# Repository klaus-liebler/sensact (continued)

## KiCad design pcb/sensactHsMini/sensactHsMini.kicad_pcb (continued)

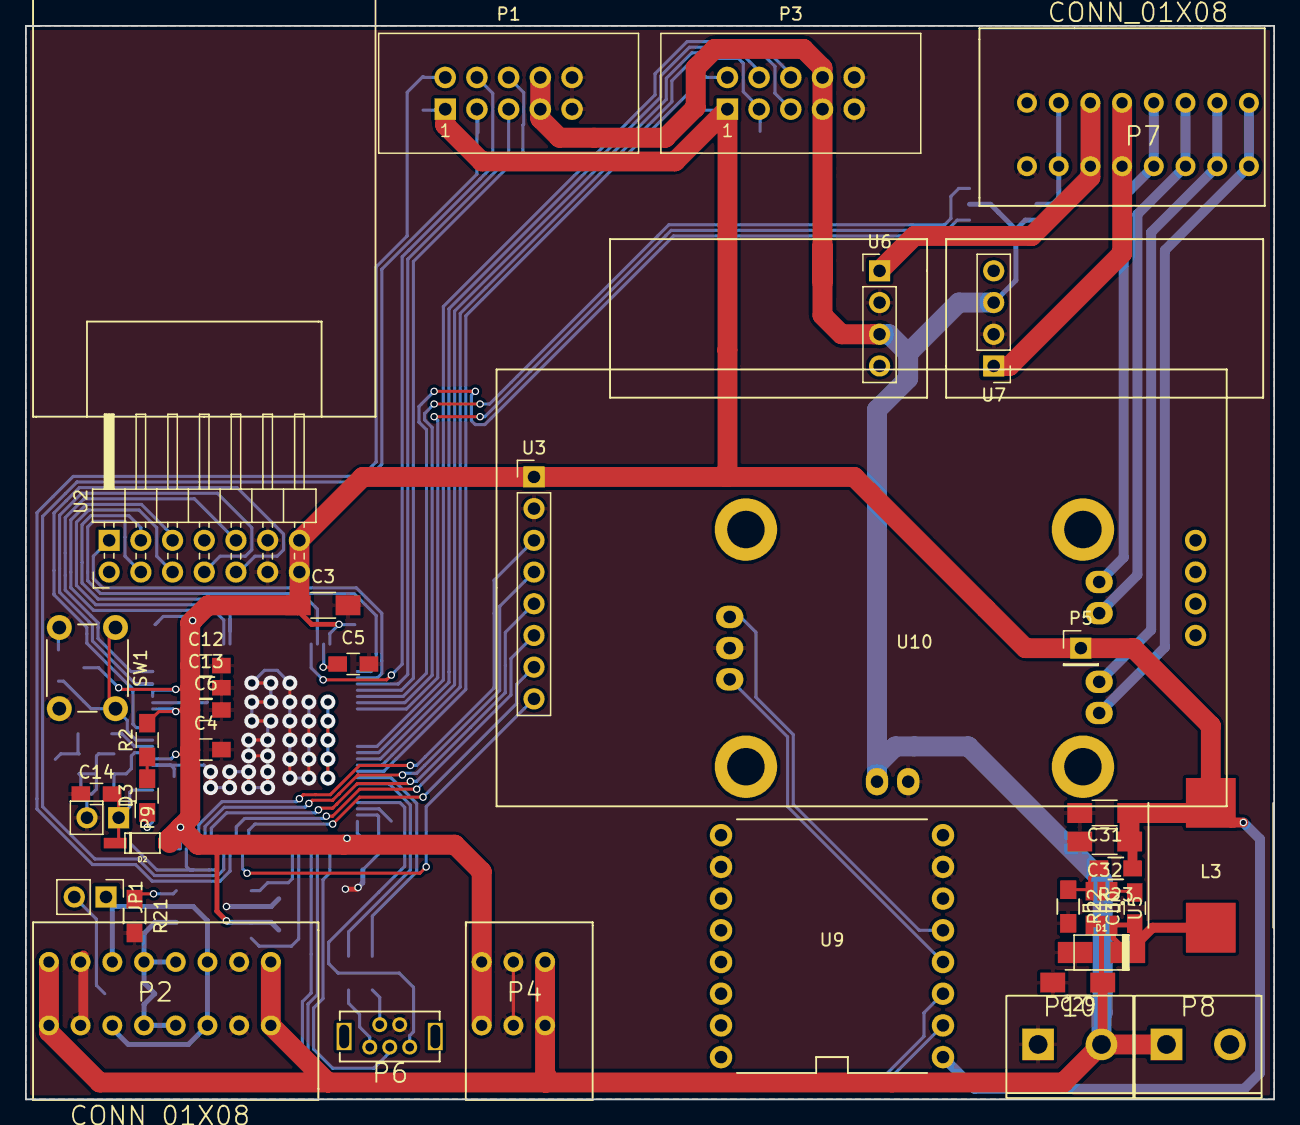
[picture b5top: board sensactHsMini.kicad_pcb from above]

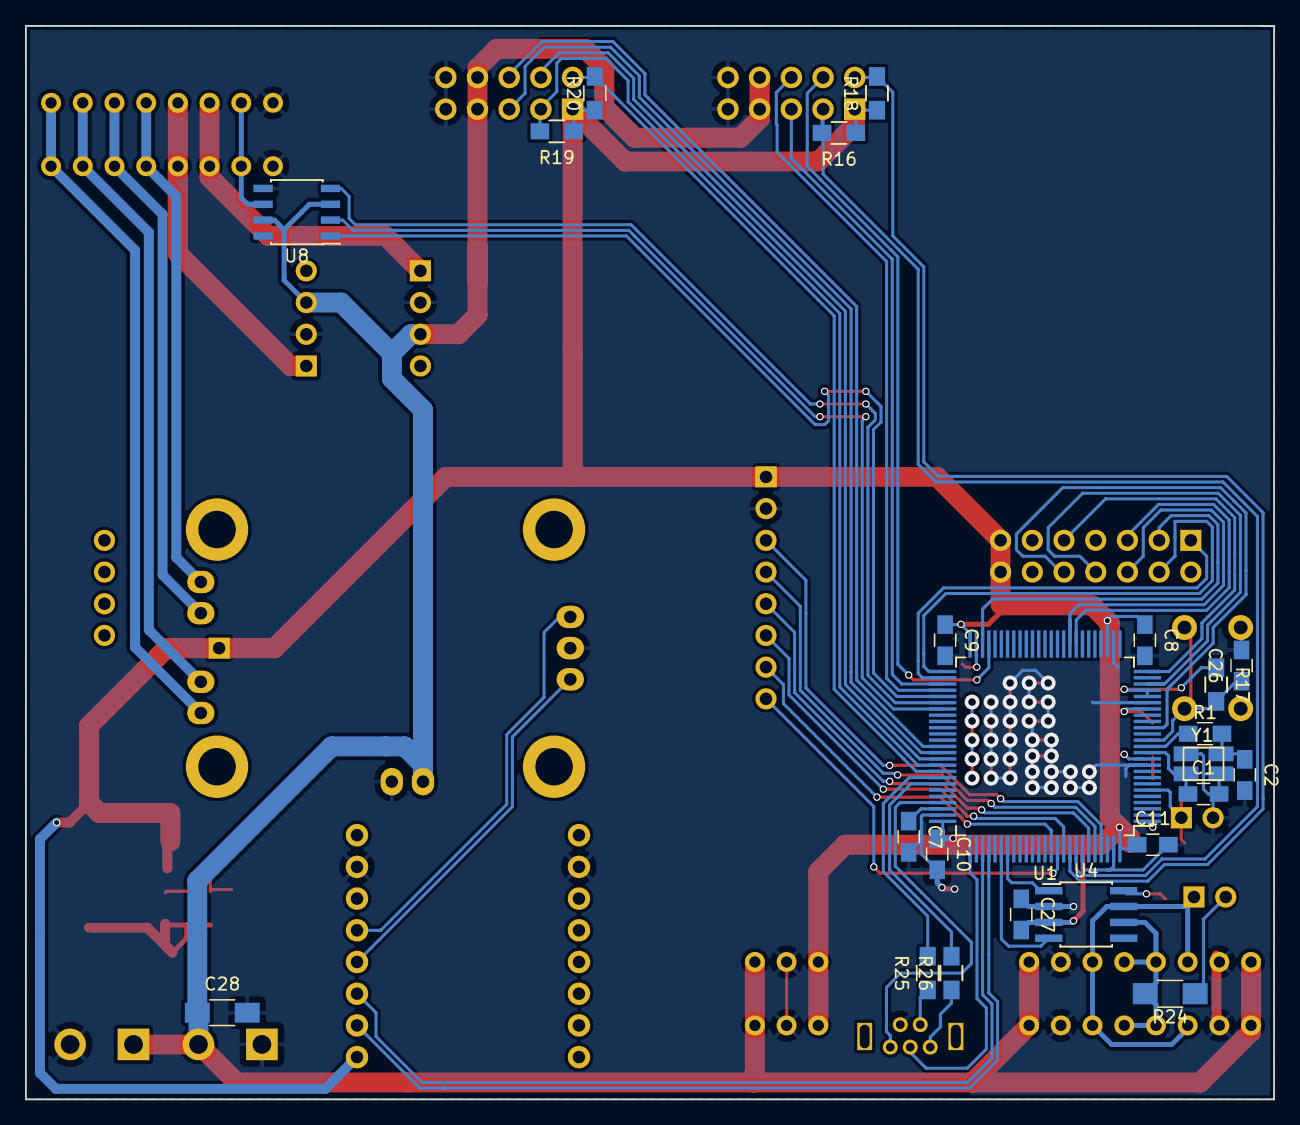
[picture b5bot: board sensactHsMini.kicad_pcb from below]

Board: 2 copper layers, 100.0 x 86.0 mm, 61 parts (23 on the bottom side), 65 nets.

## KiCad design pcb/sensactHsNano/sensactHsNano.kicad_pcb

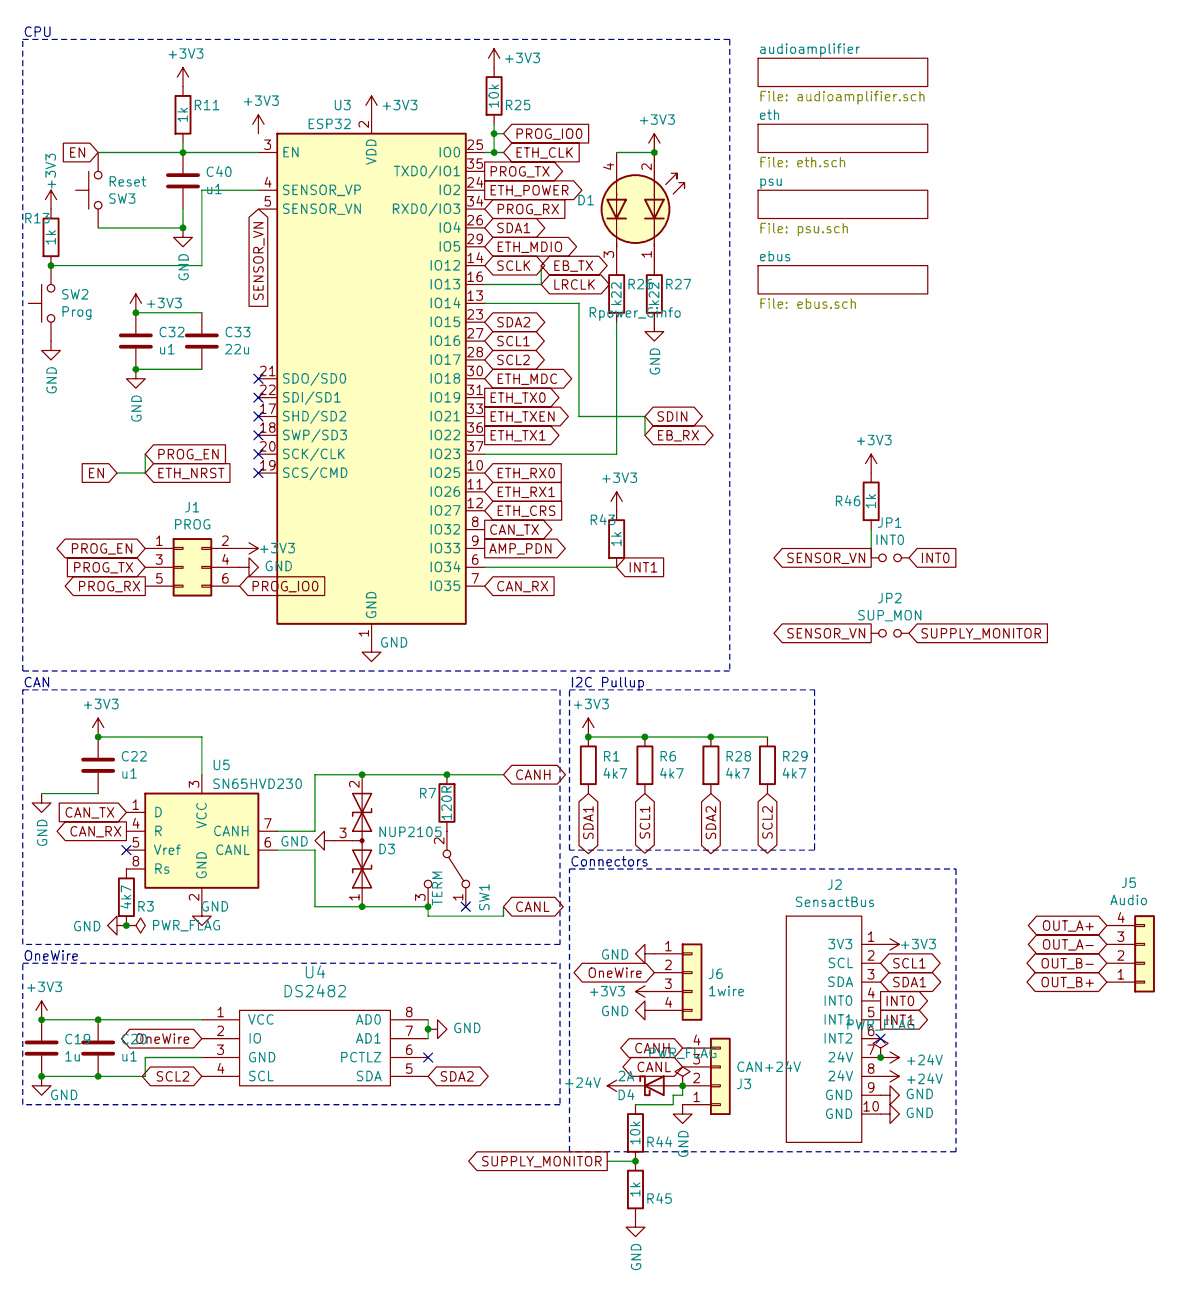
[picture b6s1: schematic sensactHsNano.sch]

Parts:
C19: 1u; C_0603_1608Metric
C20, C22, C32: u1; C_0603_1608Metric
C33: 22u; C_0805_2012Metric
C40: u1; C_0805_2012Metric_Pad1.18x1.45mm_HandSolder
D1: Rpower_Ginfo; Dialight-5530123F-0
D3: NUP2105; SOT-23_Handsoldering
D4: 2A; D_SMB_Handsoldering
J1: PROG; IDC_2x03_P1.27mm_Vertical
J2: SensactBus; IDC-Header_2x05_P2.54mm_Horizontal
J3: CAN+24V; PhoenixContact_MC_1,5_4-G-3.5_1x04_P3.50mm_Horizontal
J5: Audio; PhoenixContact_MC_1,5_4-G-3.5_1x04_P3.50mm_Horizontal
J6: 1wire; JST_XH_B4B-XH-AM_1x04_P2.50mm_Vertical
JP1: INT0; SolderJumper-2_P1.3mm_Open_RoundedPad1.0x1.5mm
JP2: SUP_MON; SolderJumper-2_P1.3mm_Open_RoundedPad1.0x1.5mm
R1, R6: 4k7; R_0603_1608Metric
R3, R28, R29: 4k7; R_0805_2012Metric_Pad1.20x1.40mm_HandSolder
R7: 120R; R_1206_3216Metric_Pad1.30x1.75mm_HandSolder
R11, R13, R43, R46: 1k; R_0805_2012Metric_Pad1.20x1.40mm_HandSolder
R25: 10k; R_0805_2012Metric_Pad1.20x1.40mm_HandSolder
R26, R27: k22; R_0805_2012Metric_Pad1.20x1.40mm_HandSolder
R44: 10k; R_0603_1608Metric
R45: 1k; R_0603_1608Metric
SW1: TERM; SW_SPDT_PCM12_handsolder
SW2: Prog; SW_Tactile_SPST_Angled_PTS645Vx58-2LFS
SW3: Reset; Button_2x4x3,5
U3: ESP32; ESP32-WROOM-32
U4: DS2482; SOIC-8_3.9x4.9mm_P1.27mm
U5: SN65HVD230; SOIC-8_3.9x4.9mm_P1.27mm

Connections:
+3V3: C19.1, C20.1, C22.1, C32.1, C33.1, D1.2 (K1), D1.4 (K2), J1.2, J2.1 (3V3), J6.3, R1.1, R6.1, R11.1, R13.1, R25.1, R28.1, R29.1, R43.1, R46.1, U3.2 (VDD), U4.1 (VCC), U5.3 (VCC); also elsewhere on the board
+24V: D4.1 (K), J2.7 (24V), J2.8 (24V); also elsewhere on the board
AMP_PDN: U3.9 (IO33); also elsewhere on the board
CANH: D3.2 (A2), J3.4, R7.2, U5.7 (CANH)
CANL: D3.1 (A1), J3.3, SW1.3 (C), U5.6 (CANL)
CAN_RX: U3.7 (IO35), U5.4 (R)
CAN_TX: U3.8 (IO32), U5.1 (D)
EB_RX: U3.13 (IO14); also elsewhere on the board
EB_TX: U3.16 (IO13); also elsewhere on the board
EN: C40.1, J1.1, R11.2, SW3.1, U3.3 (EN); also elsewhere on the board
ETH_CLK: J1.6, R25.2, U3.25 (IO0); also elsewhere on the board
ETH_CRS: U3.12 (IO27); also elsewhere on the board
ETH_MDC: U3.30 (IO18); also elsewhere on the board
ETH_MDIO: U3.29 (IO5); also elsewhere on the board
ETH_POWER: U3.24 (IO2); also elsewhere on the board
ETH_RX0: U3.10 (IO25); also elsewhere on the board
ETH_RX1: U3.11 (IO26); also elsewhere on the board
ETH_TX0: U3.31 (IO19); also elsewhere on the board
ETH_TX1: U3.36 (IO22); also elsewhere on the board
ETH_TXEN: U3.33 (IO21); also elsewhere on the board
GND: C19.2, C20.2, C22.2, C32.2, C33.2, C40.2, D3.3 (common), J1.4, J2.9 (GND), J2.10 (GND), J3.1, J6.1, J6.4, R3.2, R27.2, R45.2, SW2.1, SW3.2, U3.1 (GND), U3.15 (GND), U3.38 (GND), U3.39 (GND), U4.3 (GND), U4.7 (AD1), U4.8 (AD0), U5.2 (GND); also elsewhere on the board
INT0: J2.4 (INT0), JP1.2
INT1: J2.5 (INT1), R43.2, U3.6 (IO34)
unnamed: D1.1 (A1), R27.1
unnamed: D1.3 (A2), R26.1
unnamed: D4.2 (A), J3.2, R44.1
unnamed: R3.1, U5.8 (Rs)
unnamed: R7.1, SW1.2 (B)
unnamed: R13.2, SW2.2, U3.4 (SENSOR_VP)
unnamed: R26.2, U3.37 (IO23)
OUT_A+: J5.4; also elsewhere on the board
OUT_A-: J5.3; also elsewhere on the board
OUT_B+: J5.1; also elsewhere on the board
OUT_B-: J5.2; also elsewhere on the board
OneWire: J6.2, U4.2 (IO)
PROG_RX: J1.5, U3.34 (RXD0/IO3)
PROG_TX: J1.3, U3.35 (TXD0/IO1)
SCL1: J2.2 (SCL), R6.2, U3.27 (IO16)
SCL2: R29.2, U3.28 (IO17), U4.4 (SCL); also elsewhere on the board
SCLK: U3.14 (IO12); also elsewhere on the board
SDA1: J2.3 (SDA), R1.2, U3.26 (IO4)
SDA2: R28.2, U3.23 (IO15), U4.5 (SDA); also elsewhere on the board
SENSOR_VN: JP1.1, JP2.1, R46.2, U3.5 (SENSOR_VN)
SUPPLY_MONITOR: JP2.2, R44.2, R45.1

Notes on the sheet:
I2C Pullup
CAN
OneWire
CPU
Connectors

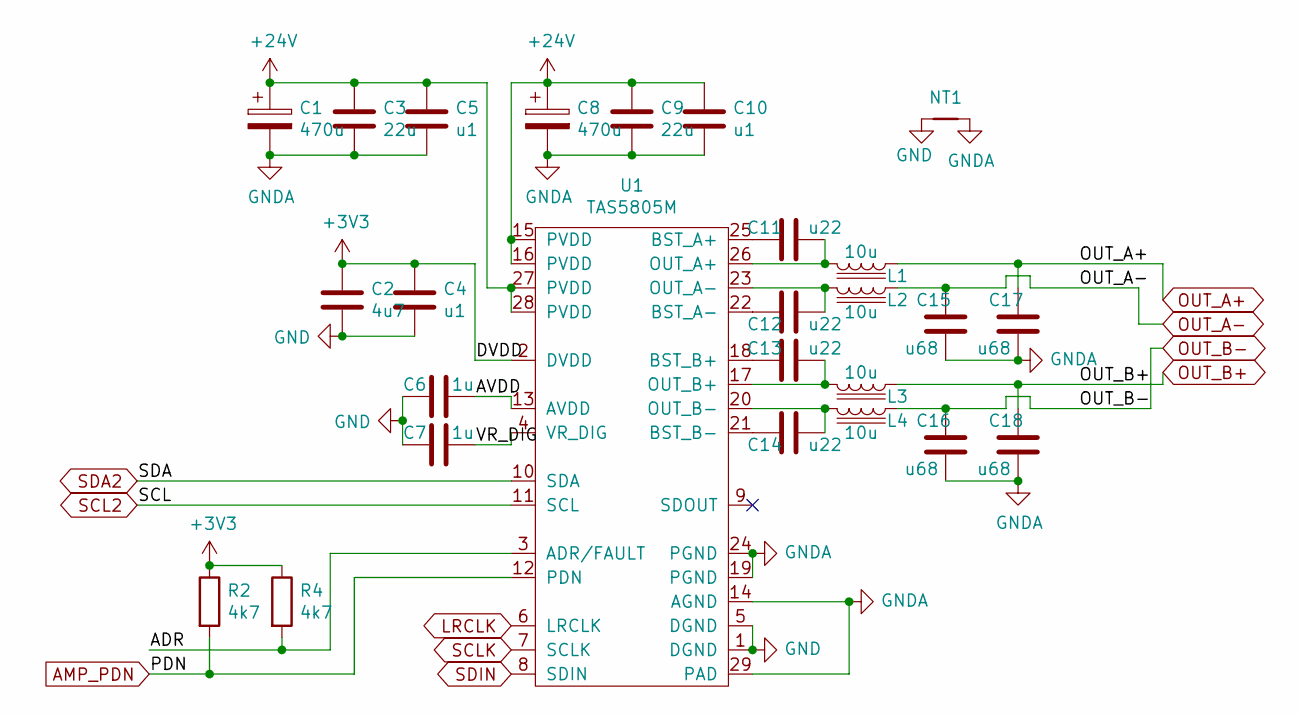
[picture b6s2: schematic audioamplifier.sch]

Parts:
C1, C8: 470u; CP_Radial_D10.0mm_P3.50mm
C2: 4u7; C_0603_1608Metric
C3, C9: 22u; C_1206_3216Metric
C4, C5, C10: u1; C_0603_1608Metric
C6, C7: 1u; C_0603_1608Metric
C11, C12, C13, C14: u22; C_0603_1608Metric
C15, C16, C17, C18: u68; C_1206_3216Metric_Pad1.33x1.80mm_HandSolder
L1, L2, L3, L4: 10u; L_1040
NT1: Net-Tie_2; NetTie-2_SMD_Pad2.0mm
R2: 4k7; R_0805_2012Metric_Pad1.20x1.40mm_HandSolder
R4: 4k7; R_0603_1608Metric
U1: TAS5805M; HTSSOP-28-1EP_4.4x9.7mm_P0.65mm_EP2.85x5.4mm_ThermalVias

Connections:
+3V3: C2.1, C4.1, R2.1, R4.1, U1.2 (DVDD); also elsewhere on the board
+24V: C1.1, C3.1, C5.1, C8.1, C9.1, C10.1, U1.15 (PVDD), U1.16 (PVDD), U1.27 (PVDD), U1.28 (PVDD); also elsewhere on the board
/audioamplifier/ADR: R4.2, U1.3 (ADR/FAULT)
/audioamplifier/AVDD: C6.1, U1.13 (AVDD)
/audioamplifier/VR_DIG: C7.1, U1.4 (VR_DIG)
AMP_PDN: R2.2, U1.12 (PDN); also elsewhere on the board
EB_RX: U1.8 (SDIN); also elsewhere on the board
EB_TX: U1.6 (LRCLK); also elsewhere on the board
GND: C2.2, C4.2, C6.2, C7.2, NT1.1, U1.1 (DGND), U1.5 (DGND); also elsewhere on the board
GNDA: C1.2, C3.2, C5.2, C8.2, C9.2, C10.2, C15.1, C16.1, C17.1, C18.1, NT1.2, U1.14 (AGND), U1.19 (PGND), U1.24 (PGND), U1.29 (PAD)
unnamed: C11.1, L1.2, U1.26 (OUT_A+)
unnamed: C11.2, U1.25 (BST_A+)
unnamed: C12.1, L2.2, U1.23 (OUT_A-)
unnamed: C12.2, U1.22 (BST_A-)
unnamed: C13.1, L3.2, U1.17 (OUT_B+)
unnamed: C13.2, U1.18 (BST_B+)
unnamed: C14.1, L4.2, U1.20 (OUT_B-)
unnamed: C14.2, U1.21 (BST_B-)
OUT_A+: C17.2, L1.1; also elsewhere on the board
OUT_A-: C15.2, L2.1; also elsewhere on the board
OUT_B+: C18.2, L3.1; also elsewhere on the board
OUT_B-: C16.2, L4.1; also elsewhere on the board
SCL2: U1.11 (SCL); also elsewhere on the board
SCLK: U1.7 (SCLK); also elsewhere on the board
SDA2: U1.10 (SDA); also elsewhere on the board

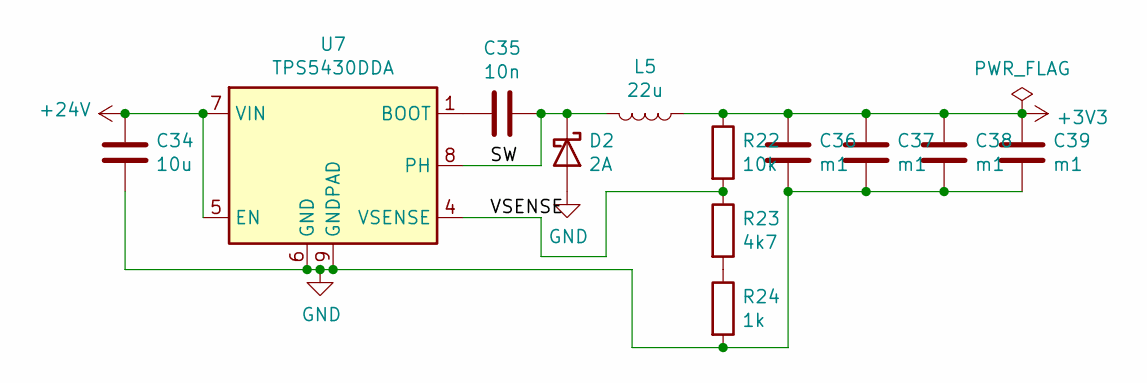
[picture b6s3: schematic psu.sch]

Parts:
C34: 10u; C_1210_3225Metric_Pad1.33x2.70mm_HandSolder
C35: 10n; C_0805_2012Metric_Pad1.18x1.45mm_HandSolder
C36, C37, C38, C39: m1; C_1210_3225Metric_Pad1.33x2.70mm_HandSolder
D2: 2A; D_SMB_Handsoldering
L5: 22u; Inductor_CDRH104_handsolder
R22: 10k; R_0805_2012Metric_Pad1.20x1.40mm_HandSolder
R23: 4k7; R_0805_2012Metric_Pad1.20x1.40mm_HandSolder
R24: 1k; R_0805_2012Metric_Pad1.20x1.40mm_HandSolder
U7: TPS5430DDA; SOIC-8_3.9x4.9mm_Pitch1.27mm_pad_handsolder

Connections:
+3V3: C36.1, C37.1, C38.1, C39.1, L5.1, R22.1; also elsewhere on the board
+24V: C34.1, U7.5 (EN), U7.7 (VIN); also elsewhere on the board
/psu/SW: C35.1, D2.1 (K), L5.2, U7.8 (PH)
/psu/VSENSE: R22.2, R23.1, U7.4 (VSENSE)
GND: C34.2, C36.2, C37.2, C38.2, C39.2, D2.2 (A), R24.2, U7.6 (GND), U7.9 (GNDPAD); also elsewhere on the board
unnamed: C35.2, U7.1 (BOOT)
unnamed: R23.2, R24.1

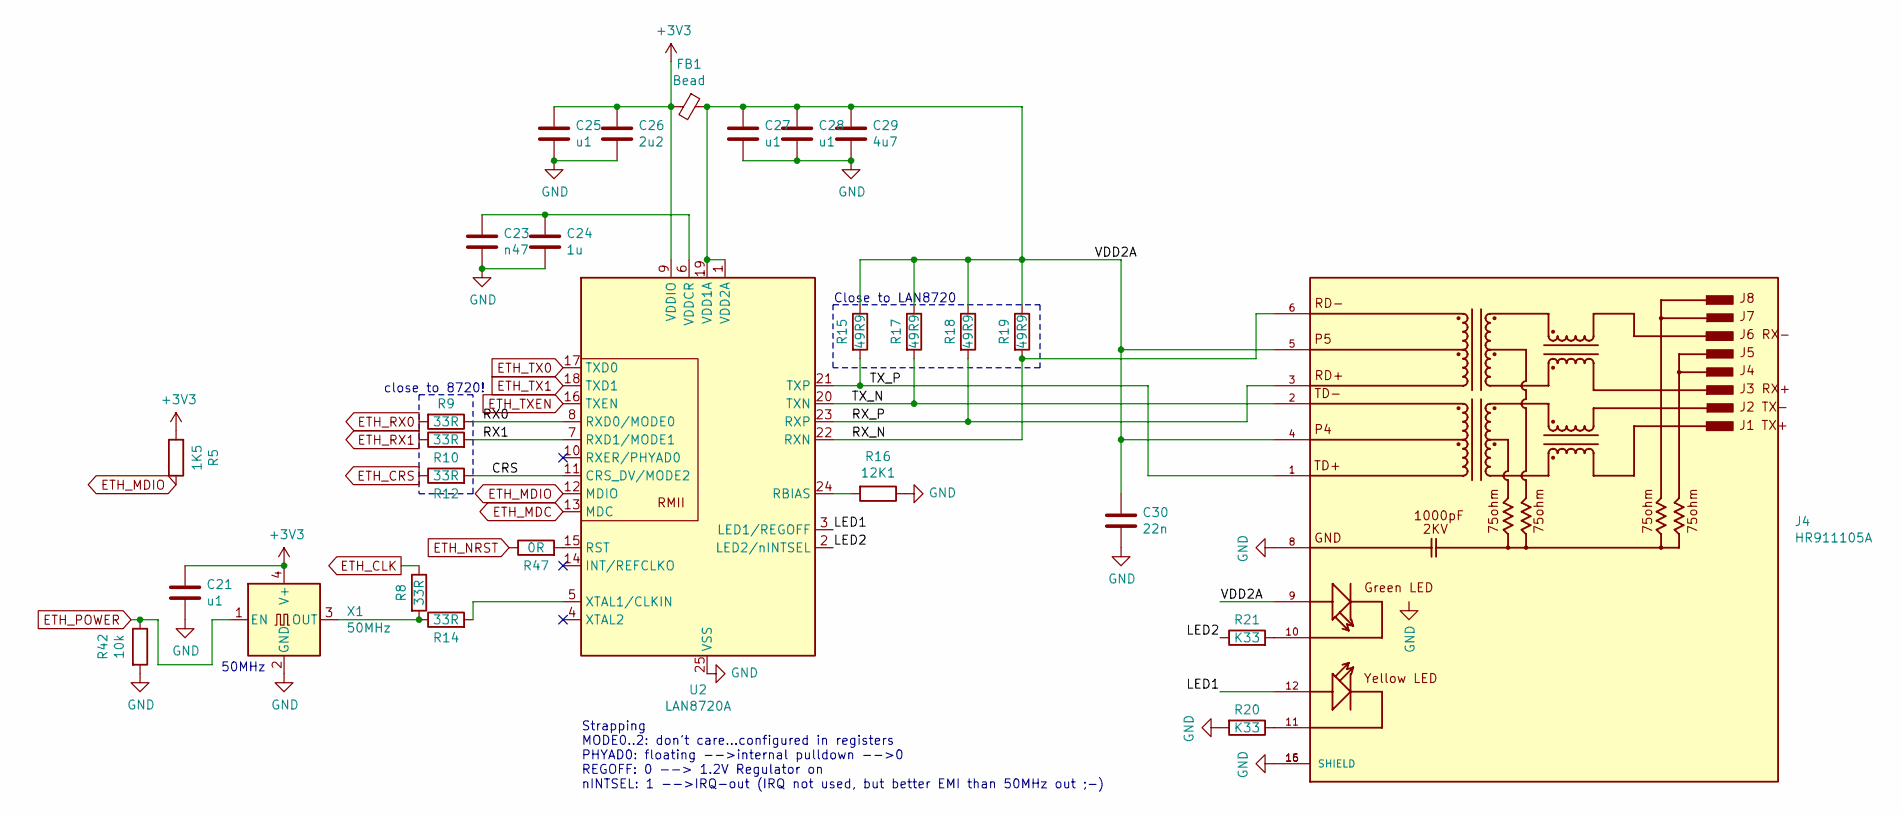
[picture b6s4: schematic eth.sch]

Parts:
C21, C25, C27, C28: u1; C_0603_1608Metric
C23: n47; C_0603_1608Metric
C24: 1u; R_0603_1608Metric
C26: 2u2; C_0603_1608Metric
C29: 4u7; C_0805_2012Metric_Pad1.18x1.45mm_HandSolder
C30: 22n; C_0805_2012Metric_Pad1.18x1.45mm_HandSolder
FB1: Bead; L_0805_2012Metric_Pad1.15x1.40mm_HandSolder
J4: HR911105A; RJ45_HANRUN_HR911105A; PARTREV A
R5: 1K5; R_0603_1608Metric
R8: 33R; R_0603_1608Metric
R9, R10, R12, R14: 33R; R_0603_1608Metric_Pad0.98x0.95mm_HandSolder
R15, R17, R18, R19: 49R9; R_0603_1608Metric
R16: 12K1; R_0603_1608Metric
R20, R21: K33; R_0805_2012Metric_Pad1.20x1.40mm_HandSolder
R42: 10k; R_0603_1608Metric_Pad0.98x0.95mm_HandSolder
R47: 0R; R_0805_2012Metric_Pad1.20x1.40mm_HandSolder
U2: LAN8720A; QFN-24-1EP_4x4mm_P0.5mm_EP2.6x2.6mm
X1: 50MHz; Oscillator_SMD_EuroQuartz_XO32-4Pin_3.2x2.5mm

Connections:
+3V3: C21.1, C25.1, C26.1, FB1.2, R5.2, U2.9 (VDDIO), X1.4 (V+); also elsewhere on the board
/eth/CRS: R12.2, U2.11 (CRS_DV/MODE2)
/eth/LED1: J4.12, U2.3 (LED1/REGOFF)
/eth/LED2: R21.1, U2.2 (LED2/nINTSEL)
/eth/RX0: R9.1, U2.8 (RXD0/MODE0)
/eth/RX1: R10.2, U2.7 (RXD1/MODE1)
/eth/RX_N: J4.6, R19.2, U2.22 (RXN)
/eth/RX_P: J4.3, R18.2, U2.23 (RXP)
/eth/TX_N: J4.2, R17.2, U2.20 (TXN)
/eth/TX_P: J4.1, R15.2, U2.21 (TXP)
/eth/VDD2A: C27.1, C28.1, C29.1, C30.1, FB1.1, J4.4, J4.5, J4.9, R15.1, R17.1, R18.1, R19.1, U2.1 (VDD2A), U2.19 (VDD1A)
EN: R47.1; also elsewhere on the board
ETH_CLK: R8.1; also elsewhere on the board
ETH_CRS: R12.1; also elsewhere on the board
ETH_MDC: U2.13 (MDC); also elsewhere on the board
ETH_MDIO: R5.1, U2.12 (MDIO); also elsewhere on the board
ETH_POWER: R42.1, X1.1 (EN); also elsewhere on the board
ETH_RX0: R9.2; also elsewhere on the board
ETH_RX1: R10.1; also elsewhere on the board
ETH_TX0: U2.17 (TXD0); also elsewhere on the board
ETH_TX1: U2.18 (TXD1); also elsewhere on the board
ETH_TXEN: U2.16 (TXEN); also elsewhere on the board
GND: C21.2, C23.2, C24.2, C25.2, C26.2, C27.2, C28.2, C29.2, C30.2, J4.8, J4.15 (SHIELD), J4.16 (SHIELD), R16.1, R20.2, R42.2, U2.25 (VSS), X1.2 (GND); also elsewhere on the board
unnamed: C23.1, C24.1, U2.6 (VDDCR)
unnamed: J4.10, R21.2
unnamed: J4.11, R20.1
unnamed: R8.2, R14.1, X1.3 (OUT)
unnamed: R14.2, U2.5 (XTAL1/CLKIN)
unnamed: R16.2, U2.24 (RBIAS)
unnamed: R47.2, U2.15 (RST)

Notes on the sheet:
50MHz
Strapping MODE0..2: don't care...configured in registers PHYAD0: floating -->internal pulldown -->0 REGOFF: 0 --> 1.2V Regulator on nINTSEL: 1 -->IRQ-out (IRQ not used, but better EMI than 50MHz out ;-)
close to 8720!
Close to LAN8720

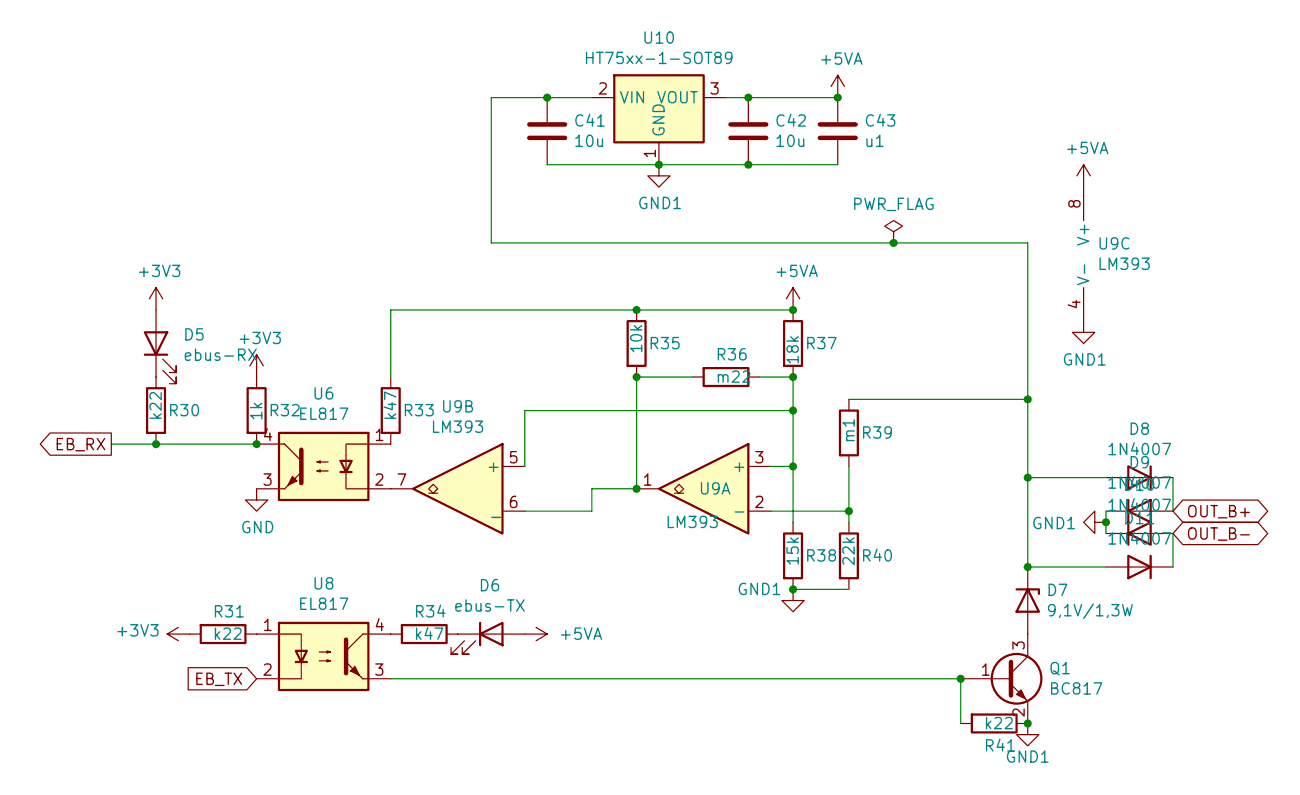
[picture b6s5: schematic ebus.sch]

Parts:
C41, C42: 10u; C_1206_3216Metric_Pad1.33x1.80mm_HandSolder
C43: u1; C_0805_2012Metric_Pad1.18x1.45mm_HandSolder
D5: ebus-RX; D_0805_2012Metric_Pad1.15x1.40mm_HandSolder
D6: ebus-TX; D_0805_2012Metric_Pad1.15x1.40mm_HandSolder
D7: 9,1V/1,3W; D_DO-41_SOD81_P10.16mm_Horizontal
D8, D9, D10, D11: 1N4007; D_SOD-123_handsolder
Q1: BC817; SOT-23_Handsoldering
R30, R31, R41: k22; R_0805_2012Metric_Pad1.20x1.40mm_HandSolder
R32: 1k; R_0805_2012Metric_Pad1.20x1.40mm_HandSolder
R33, R34: k47; R_0805_2012Metric_Pad1.20x1.40mm_HandSolder
R35: 10k; R_0805_2012Metric_Pad1.20x1.40mm_HandSolder
R36: m22; R_0805_2012Metric_Pad1.20x1.40mm_HandSolder
R37: 18k; R_0805_2012Metric_Pad1.20x1.40mm_HandSolder
R38: 15k; R_0805_2012Metric_Pad1.20x1.40mm_HandSolder
R39: m1; R_0805_2012Metric_Pad1.20x1.40mm_HandSolder
R40: 22k; R_0805_2012Metric_Pad1.20x1.40mm_HandSolder
U6, U8: EL817; SO-4_7.6x3.6mm_P2.54mm_handsolder
U9: LM393; SOIC-8_3.9x4.9mm_Pitch1.27mm_handsolder
U10: HT75xx-1-SOT89; SOT-89-3_Handsoldering

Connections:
+3V3: D5.2 (A), R31.2, R32.1; also elsewhere on the board
+5VA: C42.1, C43.1, D6.2 (A), R33.1, R35.1, R37.1, U9.8 (V+), U10.3 (VOUT)
EB_RX: R30.2, R32.2, U6.4; also elsewhere on the board
EB_TX: U8.2; also elsewhere on the board
GND: U6.3; also elsewhere on the board
GND1: C41.2, C42.2, C43.2, D9.1 (K), D10.1 (K), Q1.2 (E), R38.2, R40.2, R41.1, U9.4 (V-), U10.1 (GND)
unnamed: C41.1, D7.1 (K), D8.2 (A), D11.2 (A), R39.1, U10.2 (VIN)
unnamed: D5.1 (K), R30.1
unnamed: D6.1 (K), R34.1
unnamed: D7.2 (A), Q1.3 (C)
unnamed: Q1.1 (B), R41.2, U8.3
unnamed: R31.1, U8.1
unnamed: R33.2, U6.1
unnamed: R34.2, U8.4
unnamed: R35.2, R36.2, U9.1, U9.6 (_)
unnamed: R36.1, R37.2, R38.1, U9.3 (+), U9.5 (+)
unnamed: R39.2, R40.1, U9.2 (-)
unnamed: U6.2, U9.7
OUT_B+: D8.1 (K), D9.2 (A); also elsewhere on the board
OUT_B-: D10.2 (A), D11.1 (K); also elsewhere on the board

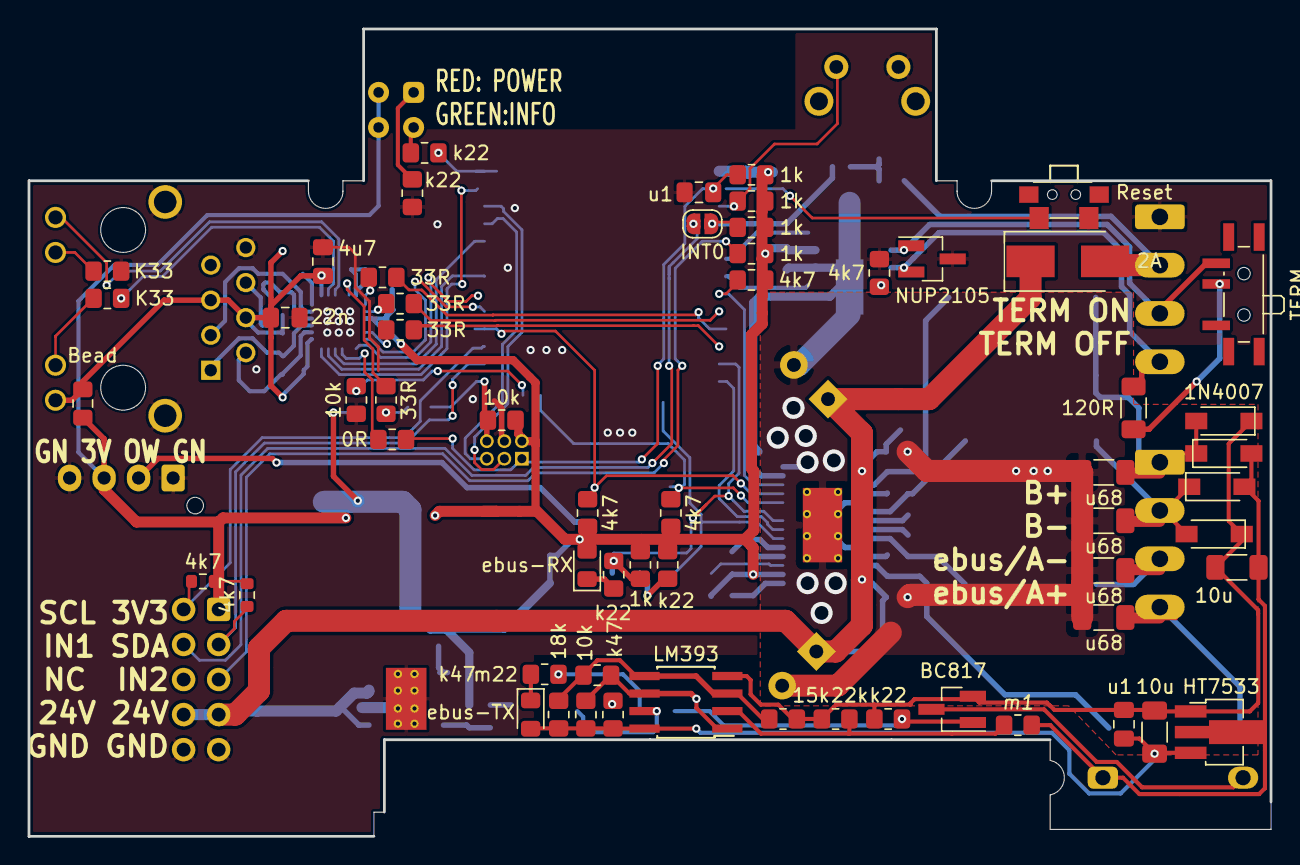
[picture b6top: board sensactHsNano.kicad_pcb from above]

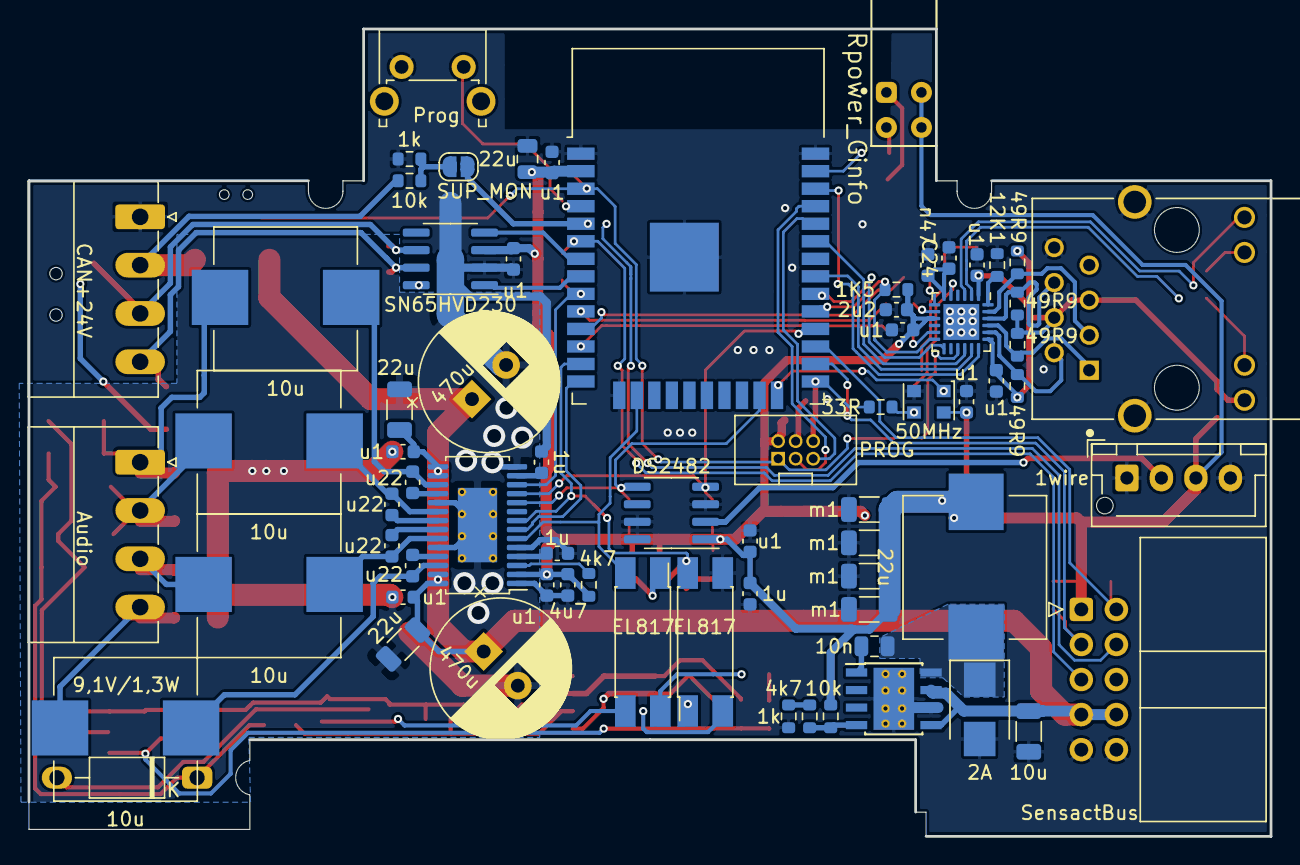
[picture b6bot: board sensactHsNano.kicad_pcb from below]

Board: 2 copper layers, 90.0 x 58.5 mm, 130 parts (71 on the bottom side), 91 nets.

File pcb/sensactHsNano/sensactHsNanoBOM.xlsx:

Reference | Quantity | Value | Footprint
C1 C8 | 2 | 470u | Capacitor_THT:CP_Radial_D10.0mm_P3.50mm
C11 C12 C13 C14 | 4 | u22 | Capacitor_SMD:C_0805_2012Metric_Pad1.18x1.45mm_HandSolder
C15 C16 C17 C18 | 4 | u68 | Capacitor_SMD:C_1206_3216Metric_Pad1.33x1.80mm_HandSolder
C2 C6 C7 C19 | 4 | 1u | Capacitor_SMD:C_0805_2012Metric_Pad1.18x1.45mm_HandSolder
C4 C5 C10 C20 C21 C22 C23 C25 C27 C28 C32 C40 C43 | 13 | u1 | Capacitor_SMD:C_0805_2012Metric_Pad1.18x1.45mm_HandSolder
C24 C26 C29 | 3 | 2u2 | Capacitor_SMD:C_0805_2012Metric_Pad1.18x1.45mm_HandSolder
C3 C9 C33 | 3 | 22u | Capacitor_SMD:C_1206_3216Metric_Pad1.33x1.80mm_HandSolder
C34 | 1 | 10u | Capacitor_SMD:C_1210_3225Metric_Pad1.33x2.70mm_HandSolder
C30 C31 C35 | 3 | 10n | Capacitor_SMD:C_0805_2012Metric_Pad1.18x1.45mm_HandSolder
C36 C37 C38 C39 | 4 | m1 | Capacitor_SMD:C_1210_3225Metric_Pad1.33x2.70mm_HandSolder
C41 C42 | 2 | 10u | Capacitor_SMD:C_1206_3216Metric_Pad1.33x1.80mm_HandSolder
D1 | 1 | Rpower_Ginfo | liebler_SEMICONDUCTORS:Dialight-5530123F-0
D3 | 1 | NUP2105 | Package_TO_SOT_SMD:SOT-23_Handsoldering
D2 D4 | 2 | 2A | Diode_SMD:D_SMB_Handsoldering
D5 | 1 | ebus-RX | Diode_SMD:D_0805_2012Metric_Pad1.15x1.40mm_HandSolder
D6 | 1 | ebus-TX | Diode_SMD:D_0805_2012Metric_Pad1.15x1.40mm_HandSolder
D7 | 1 | 9,1V/1,3W | Diode_THT:D_DO-41_SOD81_P10.16mm_Horizontal
D8 D9 D10 D11 | 4 | 1N4007 | liebler_SEMICONDUCTORS:D_SOD-123_handsolder
FB1 | 1 | Bead | Inductor_SMD:L_0805_2012Metric_Pad1.15x1.40mm_HandSolder
J1 | 1 | PROG | liebler_CONN:IDC_2x03_P1.27mm_Vertical
J2 | 1 | SensactBus | Connector_IDC:IDC-Header_2x05_P2.54mm_Horizontal
J3 | 1 | CAN+24V | Connector_Phoenix_MC:PhoenixContact_MC_1,5_4-G-3.5_1x04_P3.50mm_Horizontal
J4 | 1 | HR911105A | liebler_CONN:HANRUN_HR911105A
J5 | 1 | Audio | Connector_Phoenix_MC:PhoenixContact_MC_1,5_4-G-3.5_1x04_P3.50mm_Horizontal
J6 | 1 | 1wire | Connector_JST:JST_XH_B4B-XH-AM_1x04_P2.50mm_Vertical
JP1 | 1 | INT0 | Jumper:SolderJumper-2_P1.3mm_Open_RoundedPad1.0x1.5mm
JP2 | 1 | SUP_MON | Jumper:SolderJumper-2_P1.3mm_Open_RoundedPad1.0x1.5mm
L1 L2 L3 L4 | 4 | 10u | liebler_PASSIVES:Inductor_CDRH104_handsolder
L5 | 1 | 22u | liebler_PASSIVES:Inductor_CDRH104_handsolder
NT1 | 1 | Net-Tie_2 | NetTie:NetTie-2_SMD_Pad2.0mm
Q1 | 1 | BC817 | Package_TO_SOT_SMD:SOT-23_Handsoldering
R1 R2 R3 R4 R6 R23 R28 R29 | 8 | 4k7 | Resistor_SMD:R_0805_2012Metric_Pad1.20x1.40mm_HandSolder
R11 R13 R24 R32 R43 R45 R46 | 7 | 1k | Resistor_SMD:R_0805_2012Metric_Pad1.20x1.40mm_HandSolder
R15 R17 R18 R19 | 4 | 49R9 | Resistor_SMD:R_0805_2012Metric_Pad1.20x1.40mm_HandSolder
R16 | 1 | 12K1 | Resistor_SMD:R_0805_2012Metric_Pad1.20x1.40mm_HandSolder
R20 R21 | 2 | K33 | Resistor_SMD:R_0805_2012Metric_Pad1.20x1.40mm_HandSolder
R22 R25 R35 R42 R44 | 5 | 10k | Resistor_SMD:R_0805_2012Metric_Pad1.20x1.40mm_HandSolder
R26 R27 R30 R31 R41 | 5 | k22 | Resistor_SMD:R_0805_2012Metric_Pad1.20x1.40mm_HandSolder
R33 R34 | 2 | k47 | Resistor_SMD:R_0805_2012Metric_Pad1.20x1.40mm_HandSolder
R36 | 1 | m22 | Resistor_SMD:R_0805_2012Metric_Pad1.20x1.40mm_HandSolder
R37 | 1 | 18k | Resistor_SMD:R_0805_2012Metric_Pad1.20x1.40mm_HandSolder
R38 | 1 | 15k | Resistor_SMD:R_0805_2012Metric_Pad1.20x1.40mm_HandSolder
R39 | 1 | m1 | Resistor_SMD:R_0805_2012Metric_Pad1.20x1.40mm_HandSolder
R40 | 1 | 22k | Resistor_SMD:R_0805_2012Metric_Pad1.20x1.40mm_HandSolder
R5 | 1 | 1K5 | Resistor_SMD:R_0805_2012Metric_Pad1.20x1.40mm_HandSolder
R7 | 1 | 120R | Resistor_SMD:R_1206_3216Metric_Pad1.30x1.75mm_HandSolder
R8 R14 | 2 | k1 | Resistor_SMD:R_0805_2012Metric_Pad1.20x1.40mm_HandSolder
R9 R10 R12 | 3 | 33R | Resistor_SMD:R_0805_2012Metric_Pad1.20x1.40mm_HandSolder
SW1 | 1 | TERM | liebler_MECH:SW_SPDT_PCM12_handsolder
SW2 | 1 | Prog | Button_Switch_THT:SW_Tactile_SPST_Angled_PTS645Vx58-2LFS
SW3 | 1 | Reset | sensact:SW_SPST_2x4x3,5
U1 | 1 | TAS5805M | sensact:TSSOP-28_4.4x9.7mm_Pitch0.65mm_pad_handsolder
U10 | 1 | HT75xx-1-SOT89 | Package_TO_SOT_SMD:SOT-89-3_Handsoldering
U2 | 1 | LAN8720A | sensact:QFN-24-1EP_4x4mm_P0.5mm_EP2.6x2.6mm_handsolder
U3 | 1 | ESP32 | smopla:ESP32-WROOM-32_HANDSOLDER
U4 | 1 | DS2482 | sensact:SOIC-8_3.9x4.9mm_Pitch1.27mm_handsolder
U5 | 1 | SN65HVD230 | sensact:SOIC-8_3.9x4.9mm_Pitch1.27mm_handsolder
U6 U8 | 2 | EL817 | liebler_SEMICONDUCTORS:SO-4_7.6x3.6mm_P2.54mm_handsolder
U7 | 1 | TPS5430DDA | sensact:SOIC-8_3.9x4.9mm_Pitch1.27mm_pad_handsolder
U9 | 1 | LM393 | sensact:SOIC-8_3.9x4.9mm_Pitch1.27mm_handsolder
X1 | 1 | 50MHz | Oscillator:Oscillator_SMD_EuroQuartz_XO32-4Pin_3.2x2.5mm_HandSoldering
